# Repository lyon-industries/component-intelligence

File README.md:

<p align="center">
  
</p>

# Component Intelligence

Source-linked exact-MPN records with native KiCad 10 symbols, footprints, and
nominal STEP models for engineering agents and engineers who want an
inspectable starting point.

Use this repository to preflight a part, trace normalized data back to exact
manufacturer pages, and bring mutually consistent native assets into a design.
Do not treat it as an official manufacturer library, a substitute for your
company's library review, or approval to fabricate a board.

## Audited state

As of 2026-07-18:

- **46 complete packages** in [`catalog.json`](catalog.json)
- **6 incomplete candidates** quarantined in
  [`candidate-catalog.json`](candidate-catalog.json)
- **59 recorded integration findings**
- **0 packages claiming physical test evidence**

The browsable [`CATALOG.md`](CATALOG.md) shows every exact MPN, manufacturer,
function, package, review date, and physical-evidence state.

The catalog now includes exact-MPN examples across passives, discrete devices,
power, interfaces, logic, sensing, memory, protection, switches, and
microcontrollers. The launch additions include a 10 kΩ 0603 resistor, 100 nF
0603 MLCC, 10 µH power inductor, red 0603 LED, INA219 current monitor, and
74HC595 shift register. These are manufacturer-specific parts, not generic
value aliases.

## Use it for

- source-traceable part selection and agent retrieval
- a reviewable symbol, footprint, and mechanical-envelope starting point
- exact pin, pad, package, rating-boundary, provenance, and rights data
- catching integration constraints before schematic or layout work
- returning field corrections without silently weakening the default catalog

## Do not assume

- a `complete` package has been assembled, measured, or production-qualified
- a nominal STEP model reproduces every tolerance, marking, or lead-form detail
- a functional symbol matches your house style or preferred multi-unit layout
- the supplied paste and mask geometry fits every stencil, finish, fab, or
  assembly process
- correct component CAD makes the surrounding circuit electrically safe

## KiCad quick start

The generated project-local library tables expose only complete packages.

1. Clone the repository and pin the commit used by your design.
2. In KiCad 10, open **Preferences → Configure Paths** and add
   `COMPONENT_INTELLIGENCE_ROOT` with the absolute path to this repository.
3. For a new project with no project-specific tables, copy
   [`kicad/sym-lib-table`](kicad/sym-lib-table) and
   [`kicad/fp-lib-table`](kicad/fp-lib-table) into the project directory.
4. For an existing project, merge the desired entries through KiCad's Symbol
   and Footprint Library managers; do not overwrite existing tables.
5. Inspect the exact package suffix, pin map, pad geometry, orientation, and
   process assumptions before fabrication.

See [`QUALITY.md`](QUALITY.md) for the current KLC audit and deliberate 3D-path
deviation. `scripts/audit_kicad_native.py` reproduces the native KiCad smoke
test.

## Remote agent workflow

Consumers do not need to clone this repository or run Python. The versioned
JSON files and declared asset paths are the public interface.

1. Fetch `catalog.json` from GitHub at a pinned commit.
2. Select an exact MPN from that complete-package index.
3. Fetch the listed `component.json` path at the same commit.
4. Fetch the symbol, footprint, and STEP paths declared in that record.
5. Read the integration findings and apply the consuming toolchain's own
   approval gate.

```text
https://raw.githubusercontent.com/lyon-industries/component-intelligence/<commit>/catalog.json
https://raw.githubusercontent.com/lyon-industries/component-intelligence/<commit>/<record-path>
https://raw.githubusercontent.com/lyon-industries/component-intelligence/<commit>/<asset-path>
```

The catalog entry supplies `<record-path>`. Asset paths in `component.json` are
relative to that record's directory. Pinning one commit prevents a consumer
from mixing records and assets from different dataset states.

Treat catalog paths as repository paths, not pre-encoded URLs. URL-encode each
path segment before inserting it into a raw GitHub or Contents API URL. A
literal `%2F` in a repository path represents an encoded MPN character and must
appear as `%252F` in the request URL. Do not decode the catalog path first.

## What `complete` means

`catalog.json` contains only directories under `components/`. Admission means
the repository's current local gate found:

- an exact manufacturer, MPN, package, and official-source trail
- normalized pins, ratings, package facts, and recorded comparison methods
- deterministic native symbol and footprint replay from the canonical record
- exact symbol-pin and footprint-pad agreement, including electrical types
- copper, paste, mask, silkscreen-clearance, pin-one, fab, and courtyard checks
- a STEP file that reopens as solid geometry at the declared seating plane and
  covers the declared nominal envelope
- matching hashes, provenance, limitations, rights, and generated indexes
- no active `fabrication-stop` finding

This is a repository-local data and CAD gate. It is not independent
certification, a KiCad endorsement, or product qualification. See
[`QUALITY.md`](QUALITY.md) for the exact contract.

## Candidate work

`candidate-catalog.json` indexes directories under `candidates/`. Candidates
may contain useful source-backed facts or failure reports, but they are
excluded from the generated KiCad tables and ordinary component discovery.

The corrected INA219 SOT-23-8 candidate demonstrates this boundary: its exact
part status and pin map are retained, while an unsupported land-pattern claim
was removed and the missing DCN geometry remains a fabrication-stop finding.

## Repository layout

```text
catalog.json                    # complete packages only
candidate-catalog.json          # incomplete collaborative work
CATALOG.md                      # generated human-readable index
kicad/                          # generated complete-tier library tables
assets/component-catalog-graph.svg # generated 16:9 complete-tier graph
components/<maker>/<mpn>/       # complete package trust tier
candidates/<maker>/<mpn>/       # incomplete collaborative tier
schema/component.schema.json
scripts/build_catalog.py        # catalogs, summaries, tables, graph
scripts/generate_component_graph.py
scripts/generate_native_assets.py
scripts/validate.py             # trust-boundary and native-asset gate
```

Exact MPN spelling remains canonical in `component.json`. Repository directory
names percent-encode reserved MPN characters, while KiCad-native filenames use
a deterministic safe name. Never infer the exact MPN from a filename.

## Report a component problem

Wrong pins, pad geometry, source locators, mechanical envelopes, assembly
failures, or application constraints are useful evidence. Open a
[component error or correction](https://github.com/lyon-industries/component-intelligence/issues/new?template=component-error.yml)
with the exact MPN, pinned record, source locator, tool version, and the smallest
reproducible artifact you can share.

A serious finding against a complete package must be fixed or demoted to the
candidate tier in the same change. See [`CONTRIBUTING.md`](CONTRIBUTING.md).

## Maintainer validation

```sh
python3 -m venv .venv
. .venv/bin/activate
python -m pip install -r requirements-dev.txt
python scripts/build_catalog.py
python scripts/build_catalog.py --check
python scripts/validate.py
python -m unittest discover -s tests -v
```

## License and source rights

Original repository content is Apache-2.0. Manufacturer and product names
identify referenced parts. Linked manufacturer documents are not redistributed
or relicensed by default. Every included CAD asset records its provenance,
limitations, and source basis.

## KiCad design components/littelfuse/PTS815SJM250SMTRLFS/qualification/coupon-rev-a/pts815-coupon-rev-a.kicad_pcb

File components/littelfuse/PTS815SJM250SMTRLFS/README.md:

# PTS815SJM250SMTRLFS

Littelfuse / C&K normally-open momentary tactile switch in PTS815 J-bend SMT.

## Complete package

This directory is listed in the complete catalog and contains the verified native symbol, footprint, and STEP model.

- Identity verified: `true`
- Data cross-checked: `true`
- Native symbol verified: `true`
- Native footprint verified: `true`
- STEP model verified: `true`
- Physically tested: `false`

## Integration findings

- The official PDF is browser-readable but direct automated byte capture returned HTTP 403, so this seed does not claim a source-file hash.
- The bundled STEP file is a nominal mechanical-clearance model. It is suitable for seating, orientation, and enclosure-envelope checks, but not for internal, cosmetic, tolerance-stack, or actuator-force simulation.

## Official sources

- [PTS815 Series Microminiature SMT Top Actuated Switches](https://www.littelfuse.com/assetdocs/littelfuse-c-k-tactile-pts815-series-datasheet?assetguid=1c4ee7c5-01fd-4370-a5cc-03ec62685e73)

`component.json` is the canonical machine-readable record.

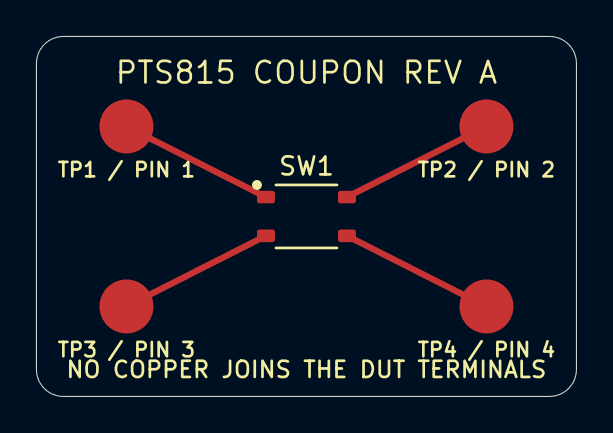
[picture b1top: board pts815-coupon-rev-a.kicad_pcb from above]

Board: 2 copper layers, 30.0 x 20.0 mm, 5 parts (0 on the bottom side), 4 nets.

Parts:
SW1: PTS815SJM250SMTRLFS
TP1: TERMINAL_1
TP2: TERMINAL_2
TP3: TERMINAL_3
TP4: TERMINAL_4

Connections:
TERMINAL_1: SW1.1, TP1.1
TERMINAL_2: SW1.2, TP2.1
TERMINAL_3: SW1.3, TP3.1
TERMINAL_4: SW1.4, TP4.1
